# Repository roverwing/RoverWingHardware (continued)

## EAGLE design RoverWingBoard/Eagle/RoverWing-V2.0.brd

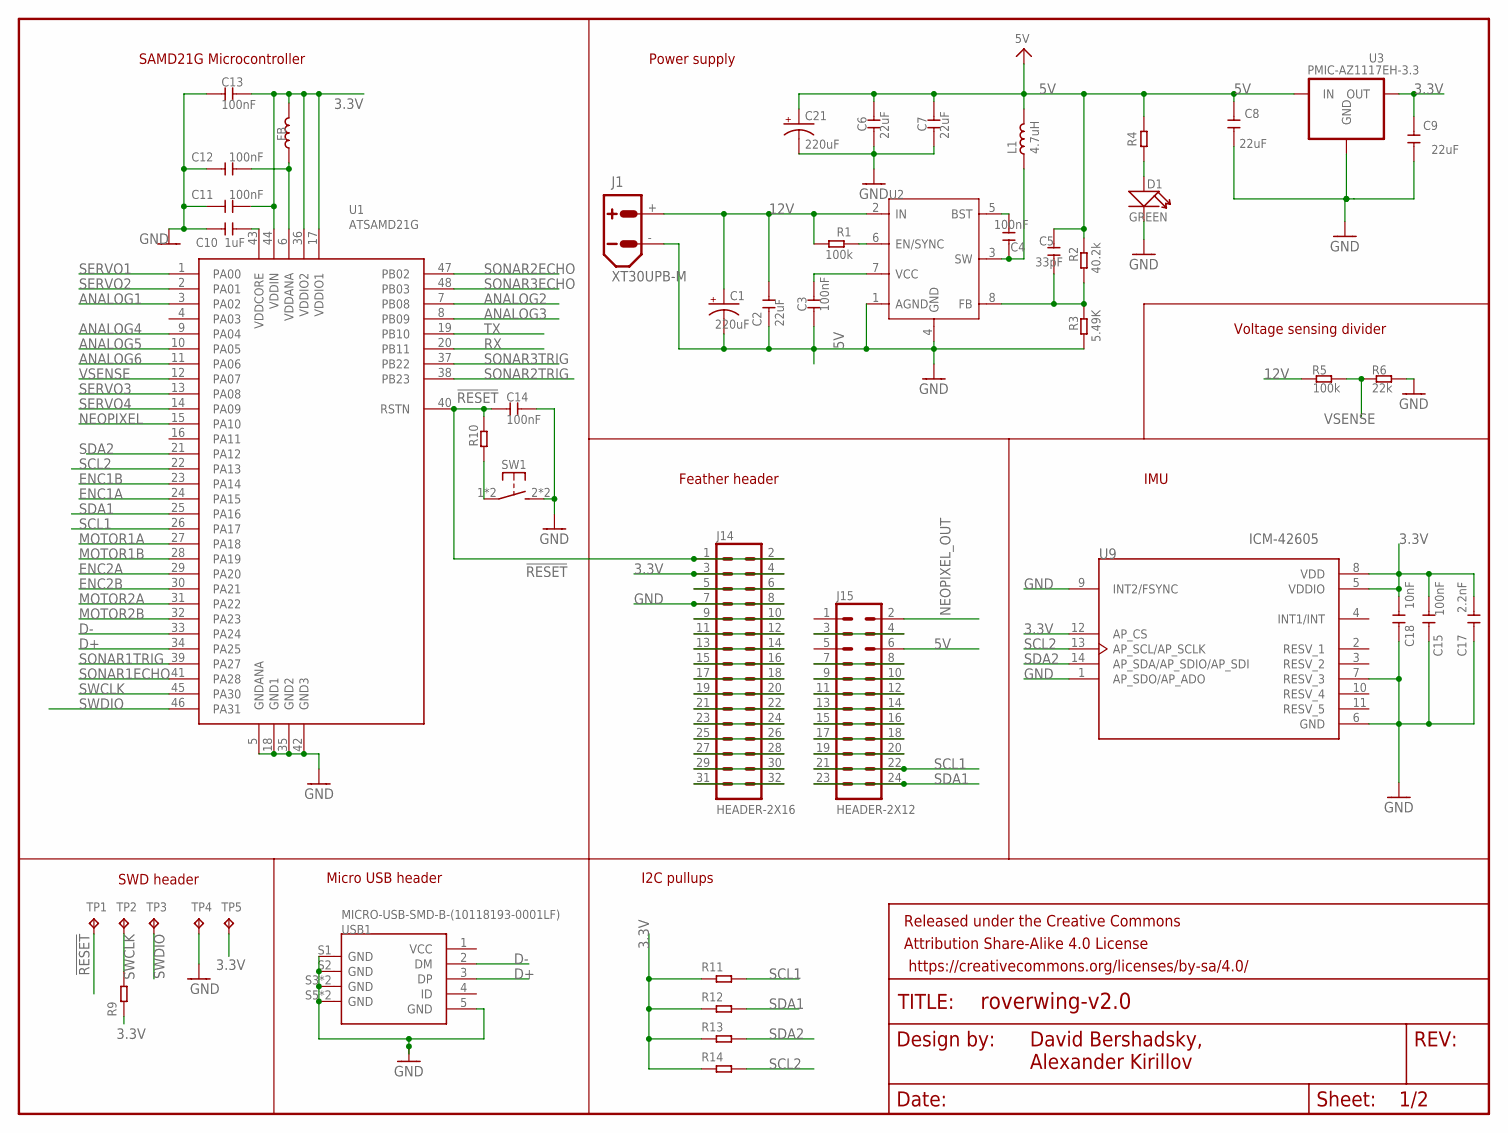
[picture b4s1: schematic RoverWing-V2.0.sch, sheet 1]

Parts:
C1, C21: 220uF; CAP-8X10.5
C2, C6, C7, C8, C9: 22uF; 0805
C3, C4, C11, C12, C13, C14, C15: 100nF; 0805
C5: 33pF; 0805
C10: 1uF; 0805
C17: 2.2nF; 0805
C18: 10nF; 0805
D1: GREEN; LED-0805
FB: 330R-1500MA; 0805
FRAME2: FRAME-LETTERNO_PACKAGE; DUMMY
J1: XT30UPB-M
J14: HEADER-2X16; 2X16
J15: HEADER-2X12; 2X12
L1: 4.7uH; IND_TDK_7.1X6.5
R1, R5: 100k; 0805
R2: 40.2k; 0805
R3: 5.49K; 0805
R4, R9, R10: 1K; R0603
R6: 22k; 0805
R11, R12, R13, R14: 1.8K; R0603
SW1: SW-TACTILE-4.5X4.5_SMD; TL3305
TP1, TP2, TP3, TP4, TP5: TPTP15R; TP15R
U1: ATSAMD21G; TQFP-48-EDITED
U2: MP2225; SOT-23-8
U3: PMIC-AZ1117EH-3.3; SOT223
U9: ICM-42605; PQFN50P300X250X97-14N
USB1: MICRO-USB-SMD-B-(10118193-0001LF); MICRO-USB5+6P-SMD-0.65-B

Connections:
3.3V: C9.2, C11.2, C13.2, C15.2, C17.2, C18.1, FB.2, J14.3, J14.4, R9.1, R11.1, R12.1, R13.1, R14.1, TP5.TP, U1.17 (VDDIO1), U1.36 (VDDIO2), U1.44 (VDDIN), U3.2 (OUT), U3.4 (OUT), U9.5 (VDDIO), U9.8 (VDD), U9.12 (AP_CS); also elsewhere on the board
5V: C5.2, C6.2, C7.2, C8.2, C21.+, J15.6, L1.2, R2.1, R4.2, U3.3 (IN); also elsewhere on the board
12V: C1.+, C2.2, J1.+, R1.2, R5.2, U2.2 (IN); also elsewhere on the board
!RESET: C14.1, J14.1, J14.2, R10.2, TP1.TP, U1.40 (RSTN)
ANALOG1: U1.3 (PA02); also elsewhere on the board
ANALOG2: U1.7 (PB08); also elsewhere on the board
ANALOG3: U1.8 (PB09); also elsewhere on the board
ANALOG4: U1.9 (PA04); also elsewhere on the board
ANALOG5: U1.10 (PA05); also elsewhere on the board
ANALOG6: U1.11 (PA06); also elsewhere on the board
BST: C4.1, U2.5 (BST)
D+: U1.34 (PA25), USB1.3 (DP)
D-: U1.33 (PA24), USB1.2 (DM)
ENC1A: U1.24 (PA15); also elsewhere on the board
ENC1B: U1.23 (PA14); also elsewhere on the board
ENC2A: U1.29 (PA20); also elsewhere on the board
ENC2B: U1.30 (PA21); also elsewhere on the board
FB: C5.1, R2.2, R3.1, U2.8 (FB)
GND: C1.-, C2.1, C3.1, C6.1, C7.1, C8.1, C9.1, C10.1, C11.1, C12.1, C13.1, C14.2, C15.1, C17.1, C18.2, C21.-, D1.-, J1.-, J14.7, J14.8, R3.2, R6.2, SW1.2 (S1), SW1.3 (S1), TP4.TP, U1.5 (GNDANA), U1.18 (GND1), U1.35 (GND2), U1.42 (GND3), U2.1 (AGND), U2.4 (GND), U3.1 (GND), U9.1 (AP_SDO/AP_ADO), U9.6 (GND), U9.7 (RESV_3), U9.9 (INT2/FSYNC), USB1.5 (GND), USB1.S1 (GND), USB1.S2 (GND), USB1.S3 (GND), USB1.S4 (GND), USB1.S5 (GND), USB1.S6 (GND); also elsewhere on the board
MOTOR1A: U1.27 (PA18); also elsewhere on the board
MOTOR1B: U1.28 (PA19); also elsewhere on the board
MOTOR2A: U1.31 (PA22); also elsewhere on the board
MOTOR2B: U1.32 (PA23); also elsewhere on the board
unnamed: J15.3, J15.4
unnamed: J15.7, J15.8
unnamed: R10.1, SW1.1, SW1.4 (P1)
unnamed: J15.9, J15.10
unnamed: C10.2, U1.43 (VDDCORE)
unnamed: J15.11, J15.12
unnamed: D1.+, R4.1
unnamed: J15.15, J15.16
unnamed: J15.13, J15.14
unnamed: R1.1, U2.6 (EN/SYNC)
unnamed: C3.2, U2.7 (VCC)
unnamed: J14.5, J14.6
unnamed: J15.17, J15.18
unnamed: J15.19, J15.20
unnamed: J14.9, J14.10
unnamed: J14.11, J14.12
unnamed: J14.13, J14.14
unnamed: J14.15, J14.16
unnamed: J14.17, J14.18
unnamed: J14.19, J14.20
unnamed: J14.21, J14.22
unnamed: J14.23, J14.24
unnamed: J14.25, J14.26
unnamed: J14.27, J14.28
unnamed: J14.29, J14.30
unnamed: J14.31, J14.32
NEOPIXEL: U1.15 (PA10); also elsewhere on the board
NEOPIXEL_OUT: J15.2; also elsewhere on the board
RX: U1.20 (PB11); also elsewhere on the board
SCL1: J15.21, J15.22, R11.2, U1.26 (PA17); also elsewhere on the board
SCL2: R14.2, U1.22 (PA13), U9.13 (AP_SCL/AP_SCLK); also elsewhere on the board
SDA1: J15.23, J15.24, R12.2, U1.25 (PA16); also elsewhere on the board
SDA2: R13.2, U1.21 (PA12), U9.14 (AP_SDA/AP_SDIO/AP_SDI); also elsewhere on the board
SERVO1: U1.1 (PA00); also elsewhere on the board
SERVO2: U1.2 (PA01); also elsewhere on the board
SERVO3: U1.13 (PA08); also elsewhere on the board
SERVO4: U1.14 (PA09); also elsewhere on the board
SONAR1ECHO: U1.41 (PA28); also elsewhere on the board
SONAR1TRIG: U1.39 (PA27); also elsewhere on the board
SONAR2ECHO: U1.47 (PB02); also elsewhere on the board
SONAR2TRIG: U1.38 (PB23); also elsewhere on the board
SONAR3ECHO: U1.48 (PB03); also elsewhere on the board
SONAR3TRIG: U1.37 (PB22); also elsewhere on the board
SW: C4.2, L1.1, U2.3 (SW)
SWCLK: R9.2, TP2.TP, U1.45 (PA30)
SWDIO: TP3.TP, U1.46 (PA31)
TX: U1.19 (PB10); also elsewhere on the board
VDDANA: C12.2, FB.1, U1.6 (VDDANA)
VSENSE: R5.1, R6.1, U1.12 (PA07)

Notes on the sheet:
SWD header
David Bershadsky, Alexander Kirillov
SAMD21G Microcontroller
Micro USB header
Power supply
Feather header
IMU
Voltage sensing divider
I2C pullups

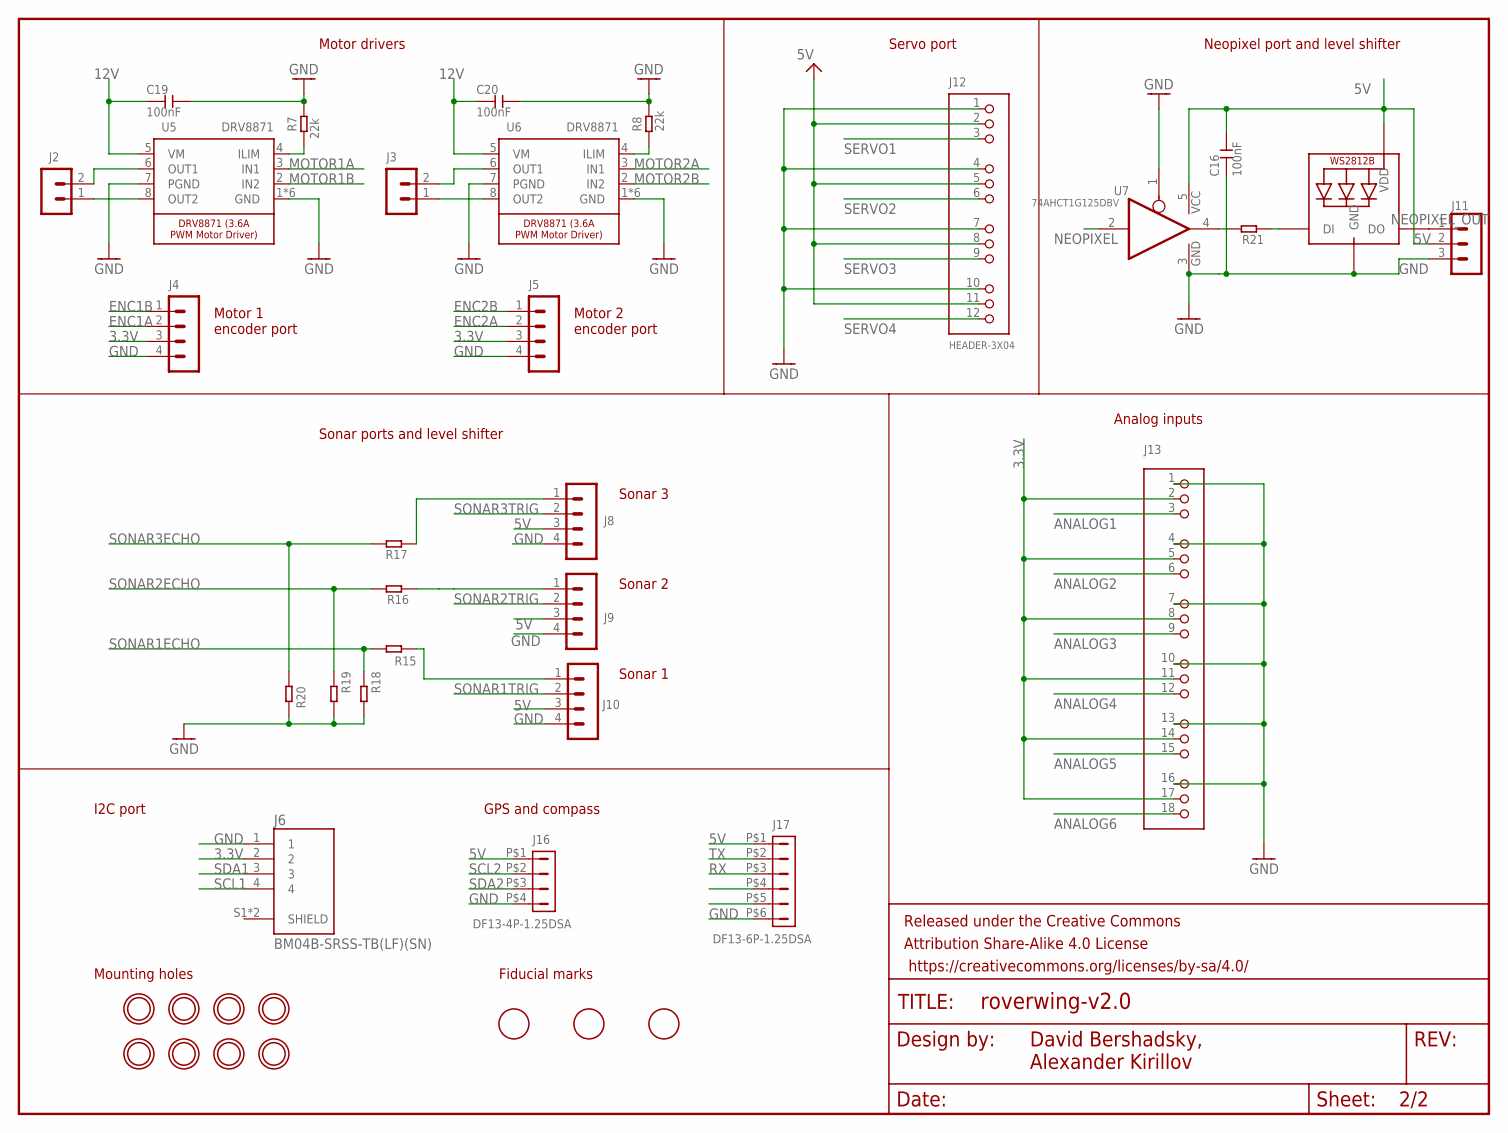
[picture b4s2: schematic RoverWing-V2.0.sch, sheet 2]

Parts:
C16, C19, C20: 100nF; 0805
D2: WS2812B3535; LED3535
FRAME1: FRAME-LETTERNO_PACKAGE; DUMMY
J2, J3: HEADER-VH; B2P-VH
J4, J5, J8, J9, J10: HEADER-PH-4P; B4B-PH-K
J6: BM04B-SRSS-TB(LF)(SN); CONN_BM04B-SRSS-TB(LF)(SN)
J11: HEADER-PH-3P; B3B-PH-K
J12: HEADER-3X04; 3X04
J13: HEADER-3X06"; 3X06
J16: DF13-4P-1.25DSA
J17: DF13-6P-1.25DSA
R7, R8: 22k; 0805
R15, R16, R17: 1K; R0603
R18, R19, R20: 1.8K; R0603
R21: 330; R0603
U5, U6: DRV8871; HSOP8
U7: 74AHCT1G125DBV; SOT23-5
U$3, U$4, U$14, U$15, U$24, U$25, U$26, U$27: MOUNTINGHOLE3.0_NPH; MOUNTINGHOLE_3.0_NPH
U$11, U$13, U$17: FIDUCIAL; FIDUCIAL_1MM

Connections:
3.3V: J4.3, J5.3, J6.2, J13.2, J13.5, J13.8, J13.11, J13.14, J13.17; also elsewhere on the board
5V: C16.2, D2.3 (VDD), J8.3, J9.3, J10.3, J11.2, J12.2, J12.5, J12.8, J12.11, J16.P$1 (1), J17.P$1 (1), U7.5 (VCC); also elsewhere on the board
12V: C19.1, C20.1, U5.5 (VM), U6.5 (VM); also elsewhere on the board
ANALOG1: J13.3; also elsewhere on the board
ANALOG2: J13.6; also elsewhere on the board
ANALOG3: J13.9; also elsewhere on the board
ANALOG4: J13.12; also elsewhere on the board
ANALOG5: J13.15; also elsewhere on the board
ANALOG6: J13.18; also elsewhere on the board
ENC1A: J4.2; also elsewhere on the board
ENC1B: J4.1; also elsewhere on the board
ENC2A: J5.2; also elsewhere on the board
ENC2B: J5.1; also elsewhere on the board
GND: C16.1, C19.2, C20.2, D2.1 (GND), J4.4, J5.4, J6.1, J8.4, J9.4, J10.4, J11.3, J12.1, J12.4, J12.7, J12.10, J13.1, J13.4, J13.7, J13.10, J13.13, J13.16, J16.P$4 (4), J17.P$6 (6), R7.2, R8.2, R18.2, R19.2, R20.2, U5.1 (GND), U5.7 (PGND), U5.GND, U5.P$1 (GND), U5.P$2 (GND), U5.P$3 (GND), U5.P$4 (GND), U6.1 (GND), U6.7 (PGND), U6.GND, U6.P$1 (GND), U6.P$2 (GND), U6.P$3 (GND), U6.P$4 (GND), U7.1 (OE), U7.3 (GND); also elsewhere on the board
MOTOR1A: U5.3 (IN1); also elsewhere on the board
MOTOR1B: U5.2 (IN2); also elsewhere on the board
MOTOR2A: U6.3 (IN1); also elsewhere on the board
MOTOR2B: U6.2 (IN2); also elsewhere on the board
unnamed: J3.1, U6.8 (OUT2)
unnamed: J3.2, U6.6 (OUT1)
unnamed: J2.1, U5.8 (OUT2)
unnamed: R21.2, U7.4 (O)
unnamed: D2.2 (DI), R21.1
unnamed: J10.1, R15.1
unnamed: J8.1, R17.1
unnamed: J2.2, U5.6 (OUT1)
unnamed: R7.1, U5.4 (ILIM)
unnamed: R8.1, U6.4 (ILIM)
unnamed: J9.1, R16.1
NEOPIXEL: U7.2 (I); also elsewhere on the board
NEOPIXEL_OUT: D2.4 (DO), J11.1; also elsewhere on the board
RX: J17.P$3 (3); also elsewhere on the board
SCL1: J6.4; also elsewhere on the board
SCL2: J16.P$2 (2); also elsewhere on the board
SDA1: J6.3; also elsewhere on the board
SDA2: J16.P$3 (3); also elsewhere on the board
SERVO1: J12.3; also elsewhere on the board
SERVO2: J12.6; also elsewhere on the board
SERVO3: J12.9; also elsewhere on the board
SERVO4: J12.12; also elsewhere on the board
SONAR1ECHO: R15.2, R18.1; also elsewhere on the board
SONAR1TRIG: J10.2; also elsewhere on the board
SONAR2ECHO: R16.2, R19.1; also elsewhere on the board
SONAR2TRIG: J9.2; also elsewhere on the board
SONAR3ECHO: R17.2, R20.1; also elsewhere on the board
SONAR3TRIG: J8.2; also elsewhere on the board
TX: J17.P$2 (2); also elsewhere on the board

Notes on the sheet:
Motor drivers
Motor 2 encoder port
Motor 1 encoder port
Sonar ports and level shifter
Analog inputs
Neopixel port and level shifter
Servo port
Sonar 3
Sonar 2
Sonar 1
Mounting holes
Fiducial marks
I2C port
GPS and compass
David Bershadsky, Alexander Kirillov

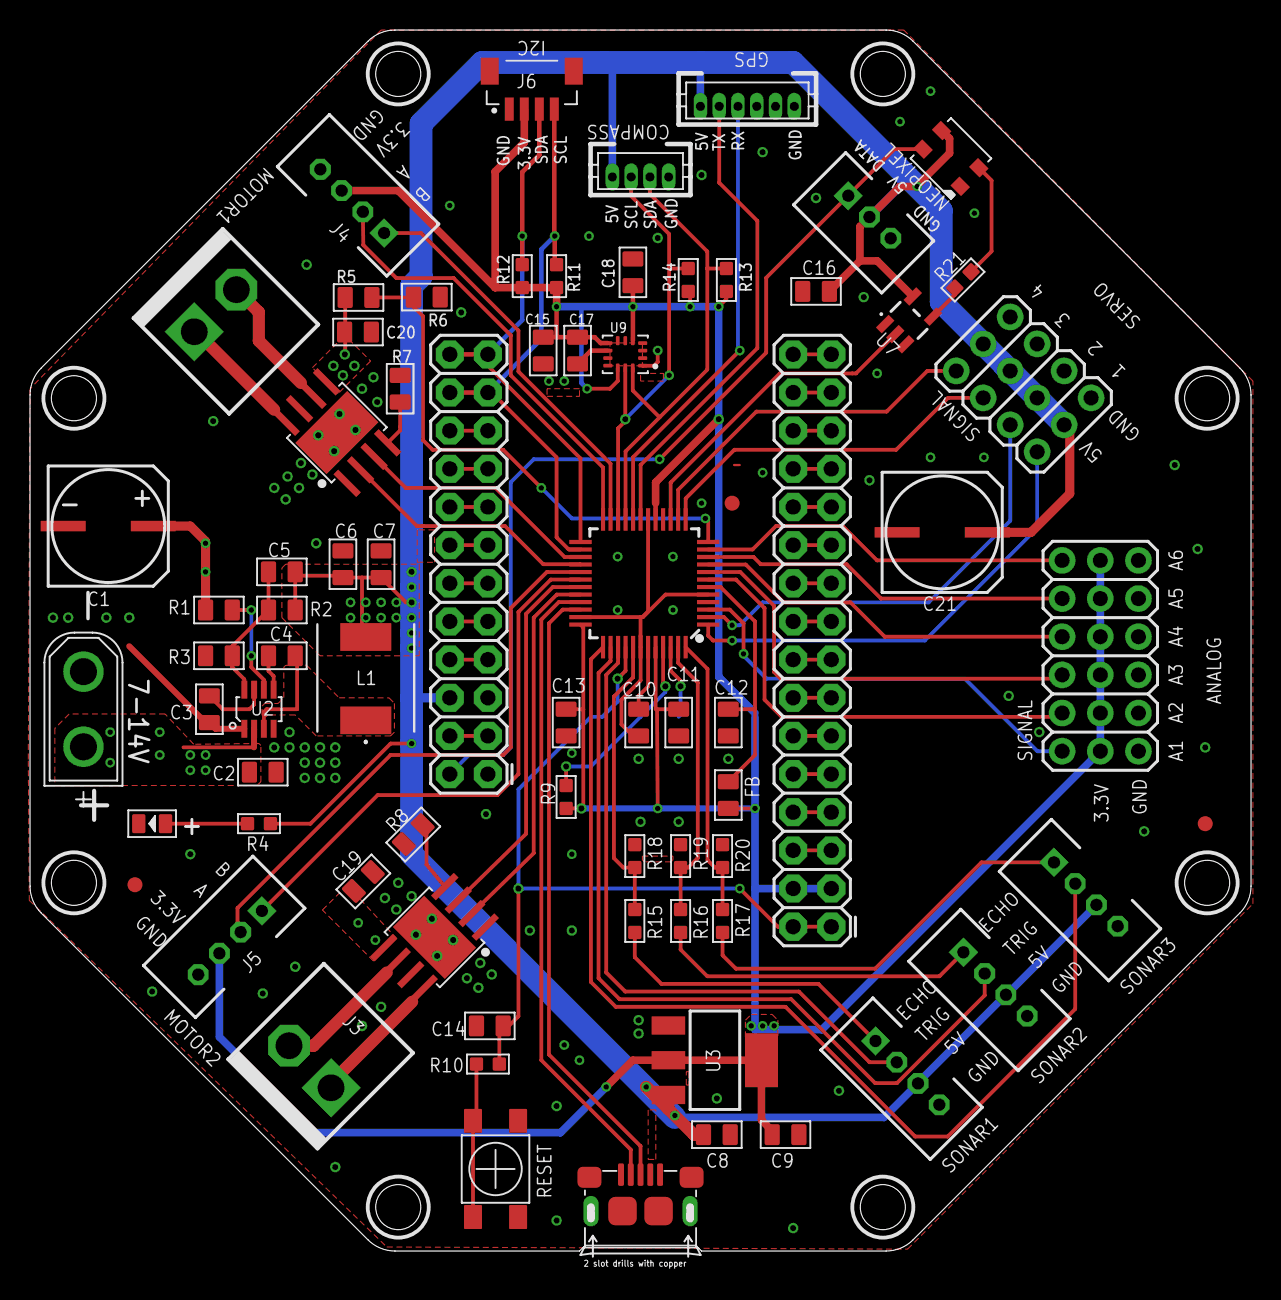
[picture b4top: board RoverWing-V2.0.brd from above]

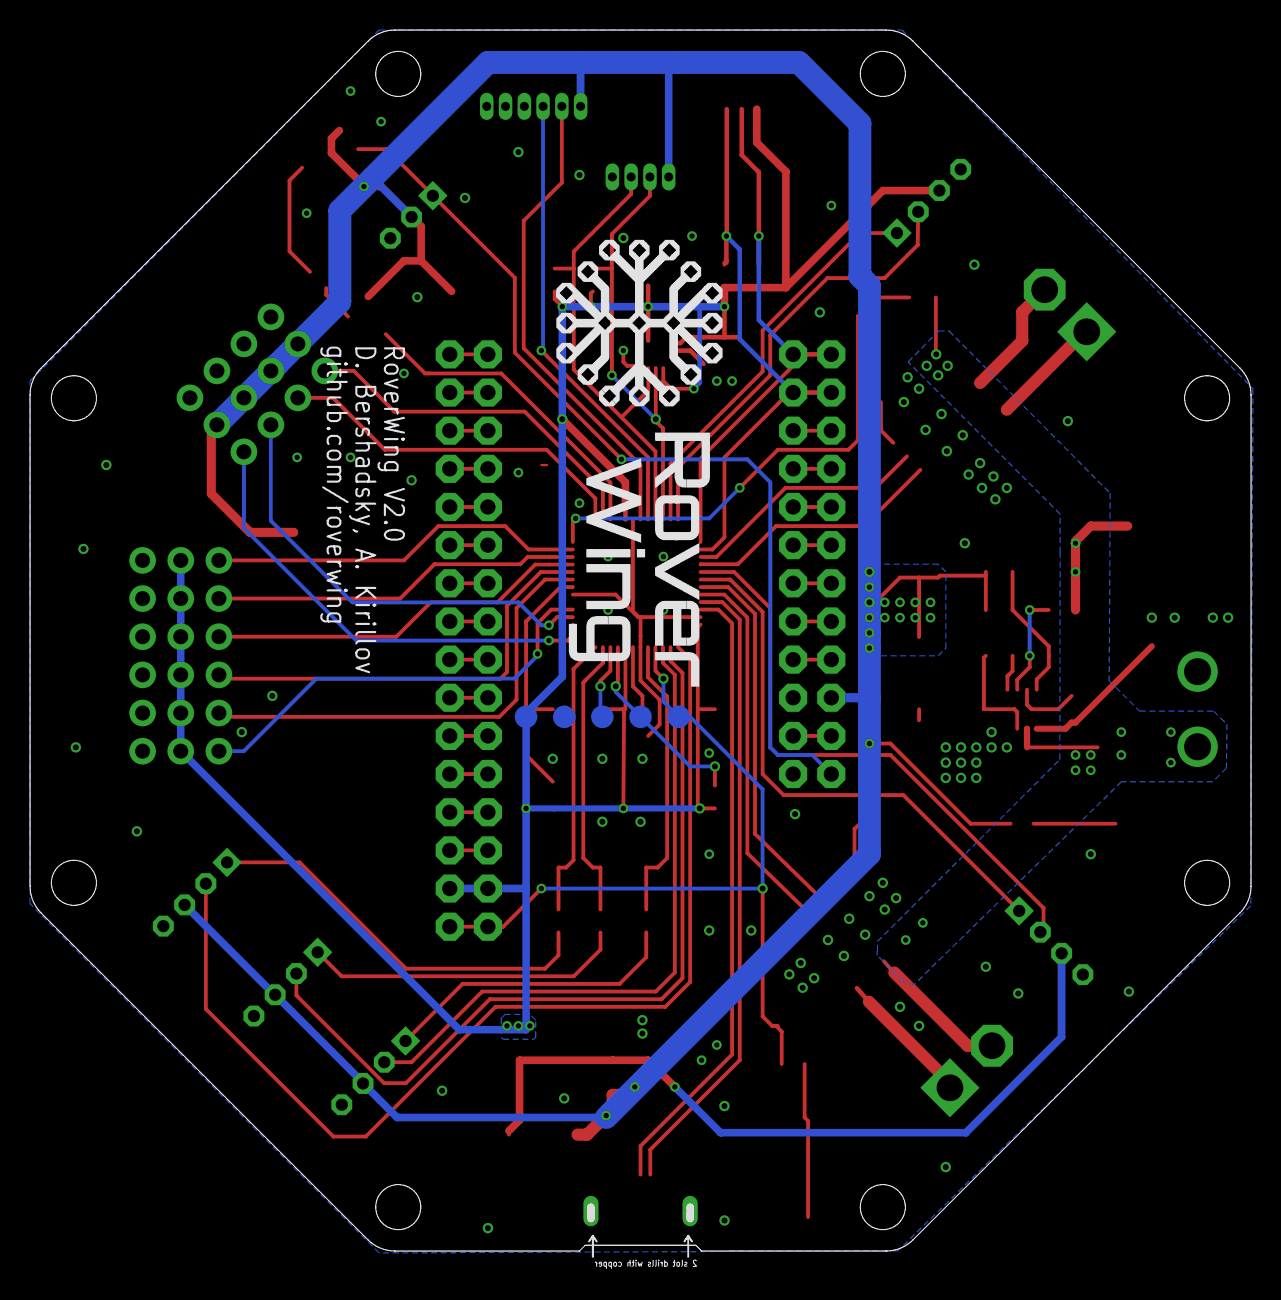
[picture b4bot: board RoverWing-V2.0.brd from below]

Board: 2 copper layers, 81.3 x 81.3 mm, 89 parts (5 on the bottom side), 83 nets.

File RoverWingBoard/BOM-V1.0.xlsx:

Parts | Qty | Value | Description | Part Num | Package | Mfg Name | Vendor | Vendor Part Num | Min quantity | Unit price | URL | Extended price
C1 | 1 | 220uF | CAP ALUM 220uF 20% 35V SMD | CK1V221MCRF10 | CAP-8X10.5 | Semtech | LCSC | C263948 | 5 | 7.2499999999999995E-2 | https://lcsc.com/product-detail/Others_Semtech-CKF1V221M0810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 | 7.2499999999999995E-2
C17 | 1 | 2.2nF | CAP CER 2.2NF 50V | C2012X7R1H222KT000N | 0805 | TDK | LCSC | C76647 | 50 | 1.52E-2 | https://lcsc.com/product-detail/Multilayer-Ceramic-Capacitor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 | 1.52E-2
C18 | 1 | 10nF | CAP CER 10NF 100V | CL21B103KCANNNC | 0805 | Samsung Electro-Mechanics | LCSC | C18741 | 50 | 1.35E-2 | https://lcsc.com/product-detail/Multilayer-Ceramic-Capacitor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 | 1.35E-2
C2, C6, C7 | 3 | 22uF | CAP CER 22uF 25V X5R | CL21A226MAQNNNE | 0805 | Samsung Electro-Mechanics | LCSC | C45783 | 5 | 0.12239999999999999 | https://lcsc.com/product-detail/Multilayer-Ceramic-Capacitor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 | 0.36719999999999997
C3, C4, C11, C12, C13, C14, C15, C16, C19, C20 | 10 | 100nF | CAP CER 0.1UF 50V | 0805B104M500NT | 0805 | Guangdong Fenghua Advanced Tech | LCSC | C286511 | 50 | 1.6899999999999998E-2 | https://lcsc.com/product-detail/Others_Guangdong-Fenghua-Adv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 | 0.16899999999999998
C5 | 1 | 33pF | CAP CER 33pF 50V | CL21C330JBANNNC | 0805 | Samsung Electro-Mechanics | LCSC | C1814 | 50 | 1.23E-2 | https://lcsc.com/product-detail/Multilayer-Ceramic-Capacitor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 | 1.23E-2
C8, C9, C10 | 3 | 1uF | CAP CER 1uF 25V | 0805B105K250AT | 0805 | Guangdong Fenghua Advanced Tech | LCSC | C111769 | 20 | 2.0299999999999999E-2 | https://lcsc.com/product-detail/Multilayer-Ceramic-Capacitor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 | 6.0899999999999996E-2
D1 | 1 | GREEN | Light Emitting Diodes (LED) Green 567.5~576.5nm 18~71mcd@20mA Top View 0805 RoHS | LTST-C170KGKT | LED-0805 | Lite-On | LCSC | C98221 | 20 | 2.76E-2 | https://lcsc.com/product-detail/Light-Emitting-Diodes-LED_LT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 | 2.76E-2
FB | 1 | 330R-1500MA | FERRITE BEAD 330 OHM 0805 1LN | BLM21PG331SN1D | 0805 | Murata Electronics | LCSC | C74764 | 20 | 3.5099999999999999E-2 | https://lcsc.com/product-detail/Ferrite-Beads-And-Chips_muRa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 | 3.5099999999999999E-2
J1, J2, J3 | 3 | HEADER-VH | CONN HEADER VH TOP 2POS 3.96MM | B2P-VH(LF)(SN) | B2P-VH | JST Sales America | LCSC | C160315 | 5 | 6.6799999999999998E-2 | * | 0.20039999999999999
J11 | 1 | HEADER-PH-3P | CONN HEADER PH TOP 3POS 2MM | B3B-PH-K-S(LF)(SN) | B3B-PH-K | JST Sales America | LCSC | C131339 | 5 | 9.9699999999999997E-2 | https://lcsc.com/product-detail/PCB-Connectors-Headers-Male-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 | 9.9699999999999997E-2
J12 | 1 | HEADER-3X04 | * | * | 3X04 | * | * | * | * | * | *
J13 | 1 | HEADER-3X06 | * | * | 3X06 | * | * | * | * | * | *
J14 | 1 | HEADER-2X16 | FEMALE HEADER 2*16 2.54MM | DS1023-2*16SF11 | 2X16 | CONNFLY Elec | LCSC | C132130 | 1 | 0.1454 | https://lcsc.com/product-detail/Female-Header_DS1023-2-16SF1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 | 0.1454
J15 | 1 | HEADER-2X12 | FEMALE HEADER 2*12 2.54MM | DS1023-2*12SF11 | 2X12 | CONNFLY Elec | LCSC | C92265 | 1 | 0.1201 | https://lcsc.com/product-detail/Female-Header_2-54Female-hea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 | 0.1201
J16 | 1 | DF13-4P-1.25DSA | CONN HEADER DF13 4POS 1.25MM | DF13-4P-1.25DSA | DF13-4P-1.25DSA | Hirose | LCSC | C202091 | 1 | 0.26550000000000001 | https://lcsc.com/product-detail/Connectors_Hirose_DF13-4P-1-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 | 0.26550000000000001
J17 | 1 | DF13-6P-1.25DSA | CONN HEADER DF13 6POS 1.25MM | DF13-6P-1.25DSA | DF13-6P-1.25DSA | Hirose | Digikey | H2195-ND | 1 | 0.33 | https://www.digikey.com/product-detail/en/hirose-electric-co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 | 0.33
J4, J5, J6, J7, J8, J9, J10 | 7 | HEADER-PH-4P | CONN HEADER PH TOP 4POS 2MM | B4B-PH-K-S(LF)(SN) | B4B-PH-K | JST Sales America | LCSC | C160257 | 10 | 5.91E-2 | https://lcsc.com/product-detail/Wire-To-Board-Wire-To-Wire-C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 | 0.41370000000000001
L1 | 1 | 4.7uH | Power Inductors 4.7uH Â±20% 5.6A | SPM6530T-4R7M | IND_TDK_7.1X6.5 | TDK | LCSC | C76857 | 10 | 0.1082 | https://lcsc.com/product-detail/Power-Inductors_TDK_SPM6530T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 | 0.1082
LED1 | 1 | WS2812B3535 | SMART LED, 3.5MM SMD | WS2812B-3535 | LED3535 | Worldsemi | LCSC | C114583 | 5 | 0.1145 | https://lcsc.com/product-detail/Light-Emitting-Diodes-LED_35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 | 0.1145
R1, R5 | 2 | 100k | RES SMD 100K OHM 1% | RC0805FR-07100KL | 0805 | YAGEO | LCSC | C96346 | 50 | 5.4000000000000003E-3 | https://lcsc.com/product-detail/Chip-Resistor-Surface-Mount_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 | 1.0800000000000001E-2
R11 | 1 | 2.7k*4 | Resistor Networks & Arrays 2.7KOhms Â±5% 1/16W 0603_x4 | RTA03-4D272JTP | 0603*4 | RALEC | LCSC | C102660 | 50 | 8.6999999999999994E-3 | https://lcsc.com/product-detail/Resistor-Networks-Arrays_2-7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 | 8.6999999999999994E-3
R2 | 1 | 40.2k | RES SMD 40.2KOhms ±1% 1/8W 0805 RoHS | RC0805FR-0740K2L | 0805 | YAGEO | LCSC | C273827 | 100 | 2.3999999999999998E-3 | https://lcsc.com/product-detail/Others_YAGEO-RC0805FR-0740K2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 | 2.3999999999999998E-3
R3 | 1 | 5.49 | RES SMD 5.49KOhms ±1% 1/8W 0805 RoHS | RC0805FR-075K49L | 0805 | YAGEO | LCSC | C273977 | 50 | 3.8E-3 | https://lcsc.com/product-detail/Others_YAGEO-RC0805FR-075K49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 | 3.8E-3
R4, R10, R109 | 3 | 1k | RES SMD 1K OHMs Â±5% 1/8W | RC0805JR-071KL | 0805 | YAGEO | LCSC | C100046 | 50 | 2.7000000000000001E-3 | https://lcsc.com/product-detail/Chip-Resistor-Surface-Mount_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 | 8.0999999999999996E-3
R6, R7, R8 | 3 | 22k | RES SMD 22KOhms Â±1% | RC0805FR-0722KL | 0805 | YAGEO | LCSC | C114565 | 50 | 4.3E-3 | https://lcsc.com/product-detail/Chip-Resistor-Surface-Mount_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 | 1.29E-2
SW1 | 1 | SW-TACTILE-4.5X4.5_SMD | Tactile Switches SPST 4.50mm x 4.50mm 0.90mm 50mA @ 12VDC SMD RoHS | TSA453G38-250 | TL3305 | BRIGHT | LCSC | C294494 | 20 | 2.5399999999999999E-2 | https://lcsc.com/product-detail/Tactile-Switches_BRIGHT-TSA4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 | 2.5399999999999999E-2
U1 | 1 | ATSAMD21G | IC MCU 32BIT 256KB FLASH 48TQFP | ATSAMD21G18A-AU | TQFP-48-EDITED | Microchip Technology | Digikey | ATSAMD21G18A-AU-ND | 1 | 3.22 | https://www.digikey.com/product-detail/en/microchip-technolo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 | 3.22
U2 | 1 | PMIC-MP2225 | DC-DC Converters Step-Down Adjustable 1 4.5V 18V 0.6V 17V 5A TSOT-23-8Â | MP2225GJ-Z | SOT-23-8 | Monolithic Power Systems | LCSC | C133066 | 10 | 0.32140000000000002 | https://lcsc.com/product-detail/DC-DC-Converters_MPS_MP2225G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 | 0.32140000000000002
U3 | 1 | AZ1117EH-3.3 | Low Dropout Regulators(LDO) Positive Fixed 1.3V @ 1A 13V 3.3V 1AÂ | AZ1117EH-3.3TRG1 | SOT223 | Diodes Inc | LCSC | C108494 | 5 | 8.1299999999999997E-2 | https://lcsc.com/product-detail/Low-Dropout-Regulators-LDO_D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 | 8.1299999999999997E-2
U4 | 1 | MPU-6050 | IMU ACCEL/GYRO 3-AXIS I2C 24QFN | MPU-6050 | QFN50P400X400X95-24N | TDK InvenSense | LCSC | C24112 | 1 | 2.8835000000000002 | https://lcsc.com/product-detail/Attitude-Sensors_TDK-InvenSe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 | 2.8835000000000002
U5, U6 | 2 | DRV8871 | Motor Drivers SO-8 RoHS | DRV8871DDAR | HSOP8 | Texas Instruments | LCSC | C75864 | 1 | 1.7250000000000001 | https://lcsc.com/product-detail/Motor-Drivers_TI_DRV8871DDAR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 | 3.45
U7 | 1 | TXS0104EPWR | Level Translators, Shifters TSSOP-14 RoHS | TXS0104EPWR | PW14 | Texas Instruments | LCSC | C44955 | 1 | 0.69340000000000002 | https://lcsc.com/product-detail/Interface-ICs_TI_TXS0104EPWR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 | 0.69340000000000002
U8 | 1 | 74AHCT1G125DBV | 74 Series Buffer, Non-Inverting 4.5V ~ 5.5V SOT-23-5 RoHS | SN74AHCT1G125DBVR | SOT23-5 | Texas Instruments | LCSC | C7484 | 5 | 0.12809999999999999 | https://lcsc.com/product-detail/74-Series_TI_SN74AHCT1G125DB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 | 0.12809999999999999
USB1 | 1 | MICRO-USB-SMD-B-(10118193-0001LF) | CONN USB MICRO B RECPT SMT R/A | 10118193-0001LF | MICRO-USB5+6P-SMD-0.65-B | Amphenol ICC | LCSC | C132562 | 1 | 0.24 | https://lcsc.com/product-detail/USB-Connectors_Amphenol_1011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 | 0.24
Total price

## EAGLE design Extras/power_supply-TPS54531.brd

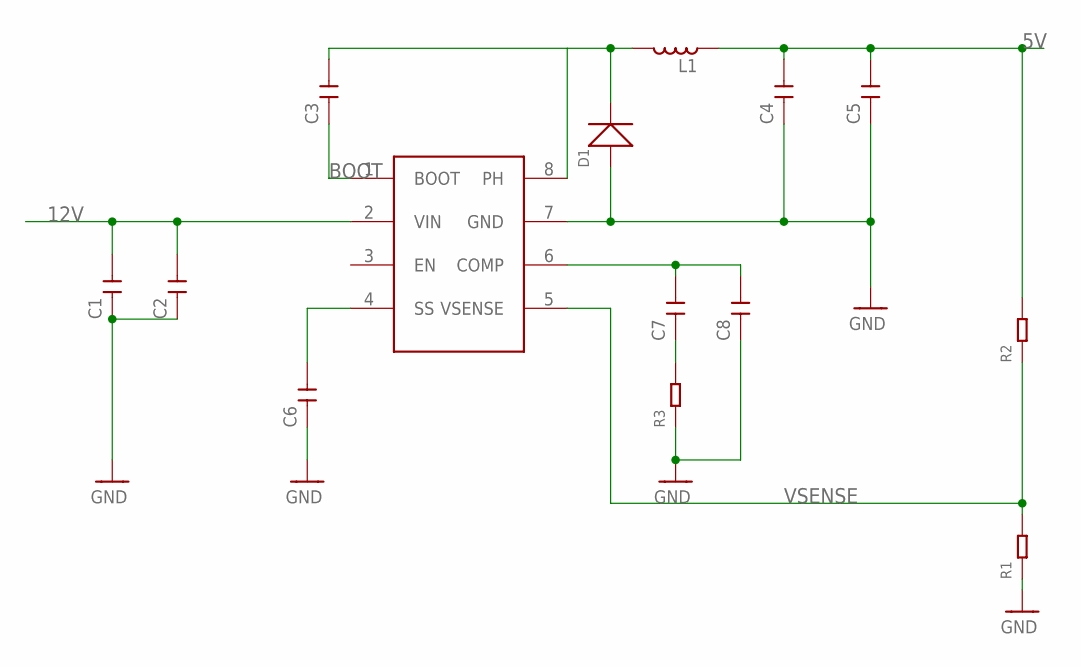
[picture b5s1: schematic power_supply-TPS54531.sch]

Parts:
C1, C2, C3, C4, C5, C6, C7, C8: CAP-CERAMIC-SMD0805; 0805
D1: SMD-DIODE-SCHOTTKY-28V-5A(DO-214AA)DO-214AC; SMA-DO214AC
L1: IND-TDK-SPM6530T; IND_TDK_7.1X6.5
R1, R2, R3: RES-SMD-0805; 0805
U$1: TPS54531SOIC8; SOIC8

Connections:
5V: C4.2, C5.2, L1.1, R2.2
12V: C1.2, C2.2, U$1.2 (VIN)
BOOT: C3.1, U$1.1 (BOOT)
GND: C1.1, C2.1, C4.1, C5.1, C6.1, C8.1, D1.A (+), R1.1, R3.1, U$1.7 (GND)
unnamed: C3.2, D1.K (-), L1.2, U$1.8 (PH)
unnamed: C6.2, U$1.4 (SS)
unnamed: C7.1, R3.2
unnamed: C7.2, C8.2, U$1.6 (COMP)
VSENSE: R1.2, R2.1, U$1.5 (VSENSE)

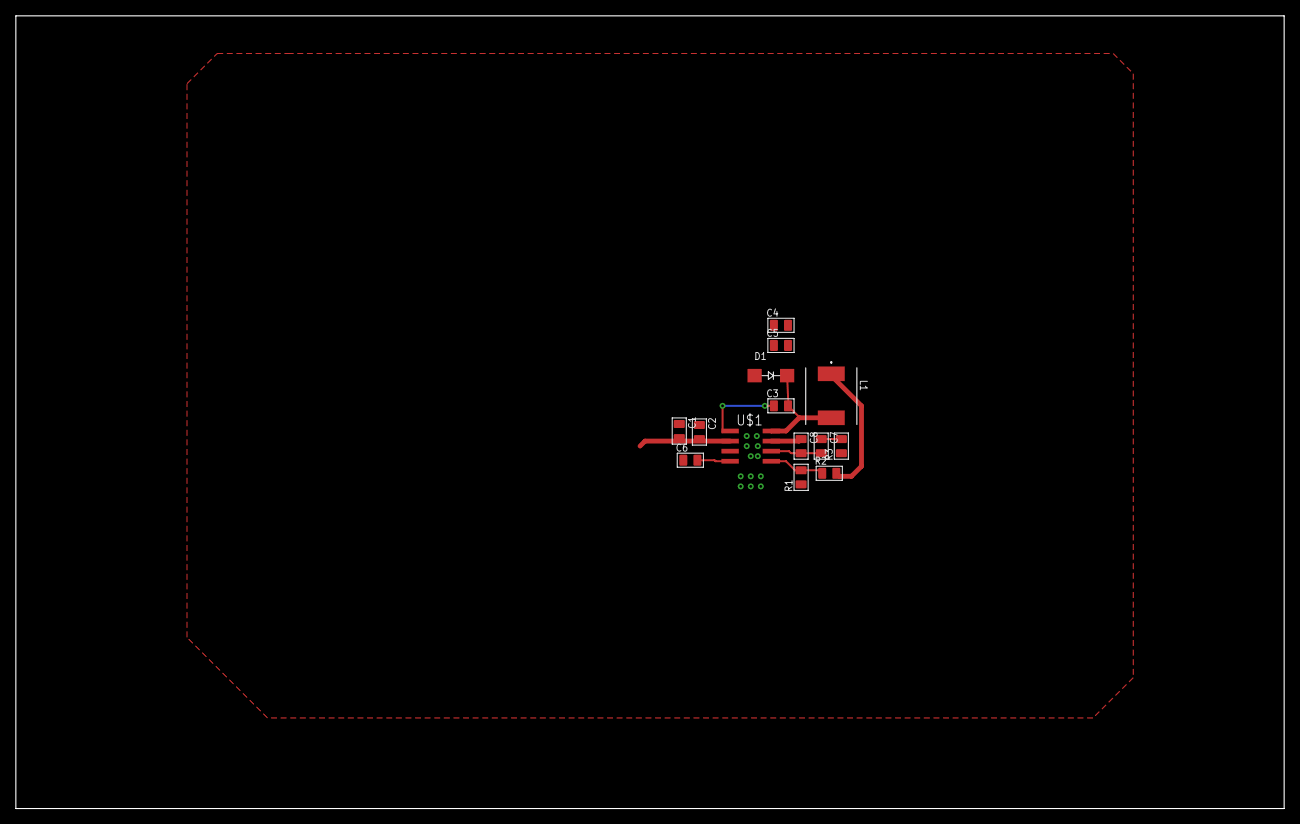
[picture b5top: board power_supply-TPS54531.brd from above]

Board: 2 copper layers, 160.0 x 100.0 mm, 14 parts (0 on the bottom side), 9 nets.

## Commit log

2019-02-10 Set theme jekyll-theme-slate
2019-02-12 Major rearrangement of files
2019-02-13 minor updates
2019-02-16 Generated gerber files
2019-02-26 Renamed README.md to README.rst
2019-03-05 V095 - fixed NeoPixel signals and added the covers
2019-03-10 Rename README.rst to README.md
2019-03-10 Rename README.md to README.rst
2019-04-21 Version 1.0
2019-04-23 Added LICENSE file, with CC-BY-SA-4.0 license
2019-04-28 Added top and bottom pdfs
2020-02-08 added png logo
2020-02-08 added logo
2020-03-28 New version, using ICM-42605 IMU
2020-03-28 making documents for ReadTheDocs
2020-03-29 Updated docs
2020-03-29 updating docs
2020-03-29 updating the docs
2020-03-29 doc reorganization
2020-03-29 doc update
2020-03-29 rearranging docs
2020-03-29 fixing links
2020-03-29 minor fixes
2020-03-29 Theming support for docs
2020-03-29 fixing theme output
2020-03-29 logo fixes
2020-03-29 fixing logos
2020-03-29 changing favicon
2020-03-29 minor fixes to documentation
2020-03-29 minor doc fixes
2020-03-31 version 1.4 of the board
2020-04-05 updating to board version 1.5;
2020-04-05 docs update
2020-04-07 README update
2020-04-07 cleaning up old files
2020-04-25 V1.6
2020-06-30 v 2.1 - new power supply
2020-07-01 board version 2.2
2020-07-02 version 2.2
2020-07-03 Repository clean up, moving old files
2020-07-05 updated schematics
2020-07-08 acknowledgment of copperforge.cc theme
2020-07-09 asd
    asd
2020-07-28 Pogo Tester design finished
2020-08-02 adding board design v2.3
2020-10-17 Finished Pogo Tester Design
2020-11-27 added code for roverwing testing jig
2020-12-18 updated to version 3.0
2020-12-23 Final version of roverwing tester code
2020-12-28 clean up; new images for docs
2020-12-28 new images for docs
2020-12-28 docs update - adding images
2021-01-16 3D printable mounting plates for RoverWings
2021-02-12 minor doc update
2021-02-12 docs update - 3d printed parts
2021-02-12 fixing typo in docs
